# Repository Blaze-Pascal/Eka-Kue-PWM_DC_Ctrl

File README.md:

# Eka-Kue-PWM_DC_Ctrl

This project involves the design of an H-bridge driver for DC motor control using PWM. It features:

    Full KiCad schematic and PCB files
    3D board visualizations
    Circuit schematics in PDF

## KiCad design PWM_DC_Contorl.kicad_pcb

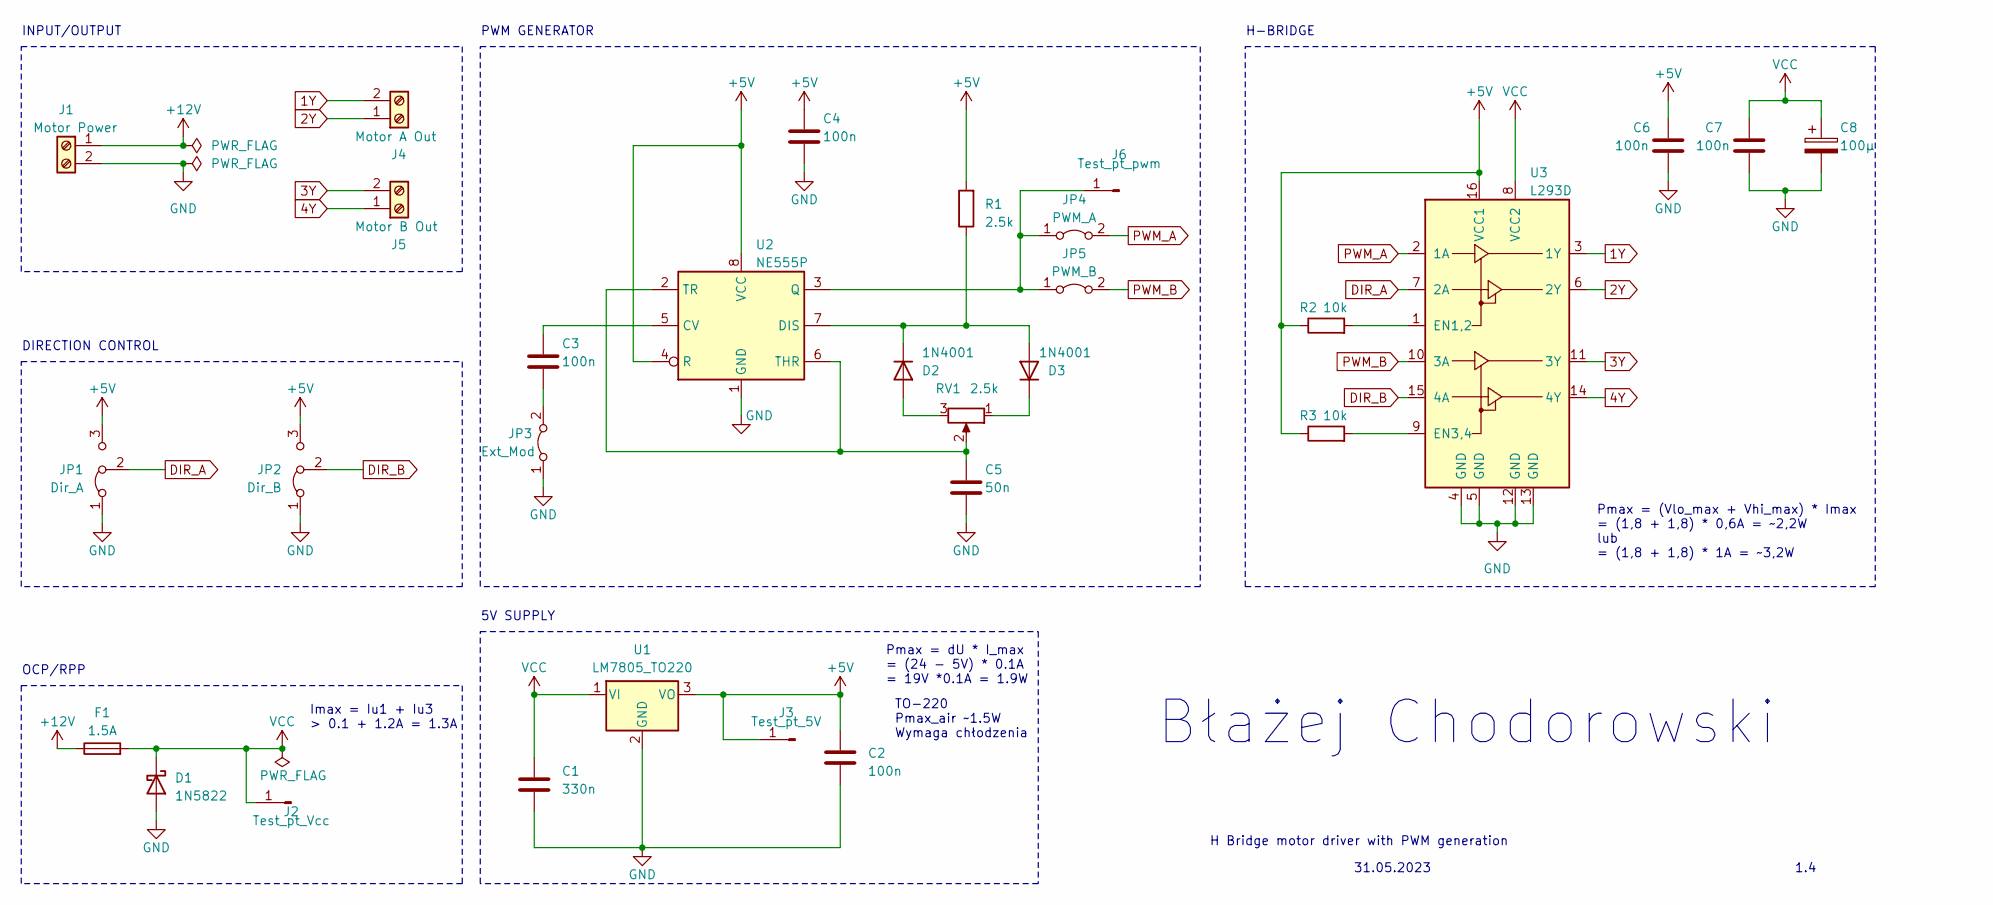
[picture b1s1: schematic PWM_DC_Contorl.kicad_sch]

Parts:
C1: 330n; C_Rect_L7.0mm_W3.5mm_P2.50mm_P5.00mm
C2, C3, C4, C6, C7: 100n; C_Rect_L7.0mm_W3.5mm_P2.50mm_P5.00mm
C5: 50n; C_Rect_L7.0mm_W3.5mm_P2.50mm_P5.00mm
C8: 100μ; CP_Radial_D10.0mm_P2.50mm_P5.00mm
D1: 1N5822; D_DO-201AD_P5.08mm_Vertical_KathodeUp
D2, D3: 1N4001; D_DO-41_SOD81_P7.62mm_Horizontal
F1: 1.5A; Fuseholder_Clip-5x20mm_Littelfuse_520_Inline_P20.50x5.80mm_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
J1: Motor Power; TerminalBlock_MetzConnect_Type055_RT01502HDWU_1x02_P5.00mm_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
J2: Test_pt_Vcc; PinHeader_1x01_P2.54mm_Vertical
J3: Test_pt_5V; PinHeader_1x01_P2.54mm_Vertical
J4: Motor A Out; TerminalBlock_MetzConnect_Type055_RT01502HDWU_1x02_P5.00mm_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
J5: Motor B Out; TerminalBlock_MetzConnect_Type055_RT01502HDWU_1x02_P5.00mm_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
J6: Test_pt_pwm; PinHeader_1x01_P2.54mm_Vertical
JP1: Dir_A; PinHeader_1x03_P2.54mm_Vertical
JP2: Dir_B; PinHeader_1x03_P2.54mm_Vertical
JP3: Ext_Mod; PinHeader_2x01_P2.54mm_Vertical
JP4: PWM_A; PinHeader_2x01_P2.54mm_Vertical
JP5: PWM_B; PinHeader_2x01_P2.54mm_Vertical
R1: 2.5k; R_Axial_DIN0207_L6.3mm_D2.5mm_P7.62mm_Horizontal
R2, R3: 10k; R_Axial_DIN0207_L6.3mm_D2.5mm_P7.62mm_Horizontal
RV1: 2.5k; PinHeader_1x03_P2.54mm_Vertical
U1: LM7805_TO220; TO-220-3_Horizontal_TabDown
U2: NE555P; DIP-8
U3: L293D; DIP-16_W7.62mm_LongPads

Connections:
1Y: J4.2, U3.3 (1Y)
2Y: J4.1, U3.6 (2Y)
3Y: J5.2, U3.11 (3Y)
4Y: J5.1, U3.14 (4Y)
+5V: C2.1, C4.1, C6.1, J3.1, JP1.3 (B), JP2.3 (B), R1.2, R2.1, R3.1, U1.3 (VO), U2.4 (R), U2.8 (VCC), U3.16 (VCC1)
+12V: F1.1, J1.1
DIR_A: JP1.2 (C), U3.7 (2A)
DIR_B: JP2.2 (C), U3.15 (4A)
GND: C1.2, C2.2, C4.2, C5.2, C6.2, C7.2, C8.2, D1.2 (A), J1.2, JP1.1 (A), JP2.1 (A), JP3.1 (A), U1.2 (GND), U2.1 (GND), U3.4 (GND), U3.5 (GND), U3.12 (GND), U3.13 (GND); also elsewhere on the board
unnamed: D2.2 (A), RV1.3
unnamed: D2.1 (K), D3.2 (A), R1.1, U2.7 (DIS)
unnamed: D3.1 (K), RV1.1
unnamed: J6.1, JP4.1 (A), JP5.1 (A), U2.3 (Q)
unnamed: C3.2, JP3.2 (B)
unnamed: C3.1, U2.5 (CV)
unnamed: C5.1, RV1.2, U2.2 (TR), U2.6 (THR)
unnamed: R2.2, U3.1 (EN1,2)
unnamed: R3.2, U3.9 (EN3,4)
PWM_A: JP4.2 (B), U3.2 (1A)
PWM_B: JP5.2 (B), U3.10 (3A)
VCC: C1.1, C7.1, C8.1, D1.1 (K), F1.2, J2.1, U1.1 (VI), U3.8 (VCC2)

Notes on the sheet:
DIRECTION CONTROL
H-BRIDGE
31.05.2023
1.4
TO-220 Pmax_air ~1.5W Wymaga chłodzenia
Pmax = dU * I_max = (24 - 5V) * 0.1A = 19V *0.1A = 1.9W
Pmax = (Vlo_max + Vhi_max) * Imax = (1,8 + 1,8) * 0,6A = ~2,2W lub = (1,8 + 1,8) * 1A = ~3,2W
OCP/RPP
Imax = Iu1 + Iu3 > 0.1 + 1.2A = 1.3A
5V SUPPLY
Błażej Chodorowski
INPUT/OUTPUT
H Bridge motor driver with PWM generation
PWM GENERATOR

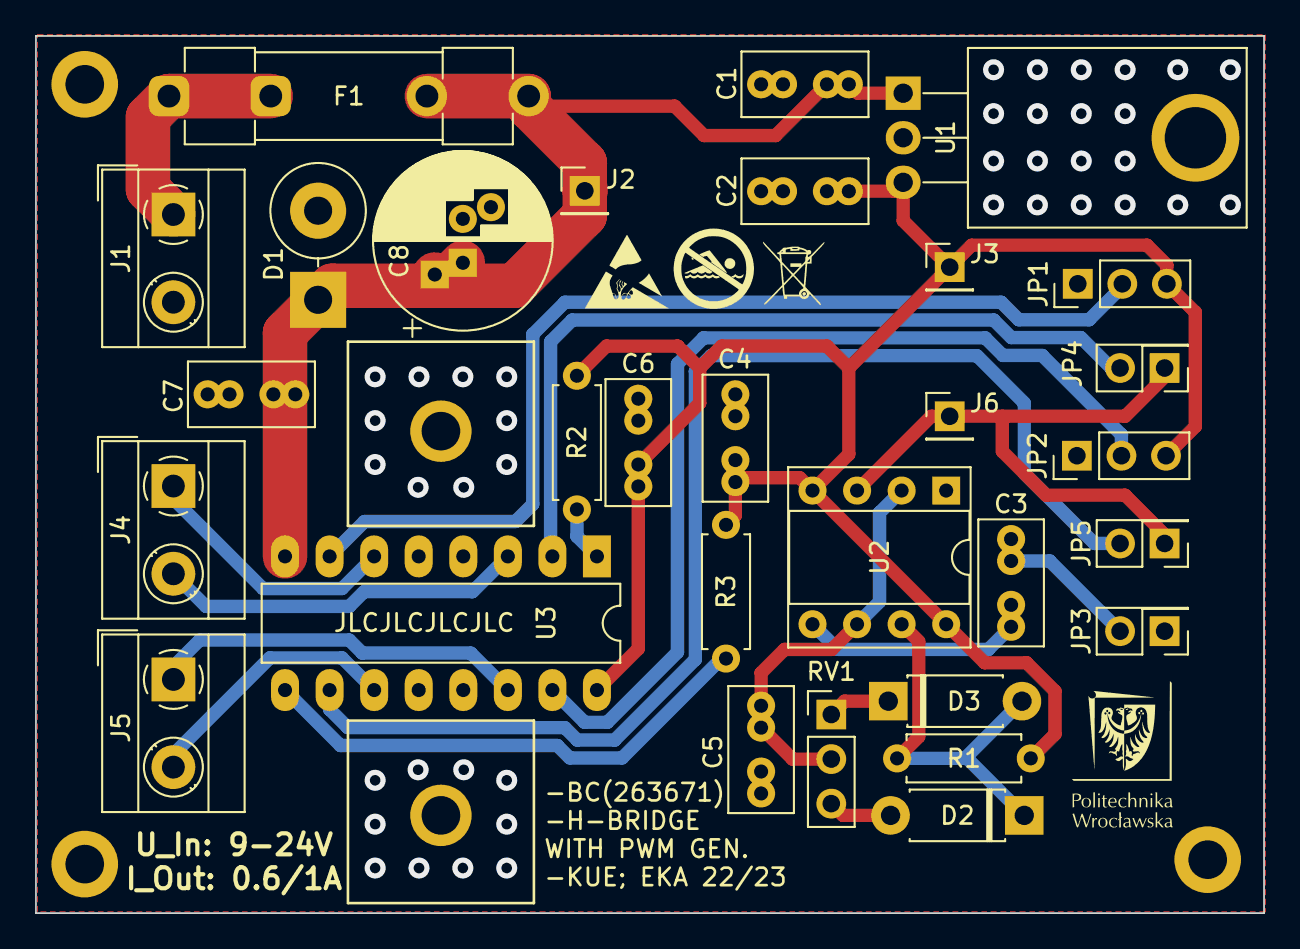
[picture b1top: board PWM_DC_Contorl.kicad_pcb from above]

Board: 2 copper layers, 70.0 x 50.0 mm, 39 parts (0 on the bottom side), 21 nets.

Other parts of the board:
G1: LOGO; swim
G2: LOGO; esd
G3: LOGO; pwr
G4: LOGO; trash
REF1, REF2, REF3: MountingHole_2.2mm_M2_DIN965_Pad
REF41, REF42: MountingHole_2.2mm_M2_ISO7380_Pad

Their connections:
GND: REF41.1, REF42.1; also elsewhere on the board

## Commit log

2024-03-20 KiCad schematic and board design
2024-03-20 Added screenshots for quick reference
